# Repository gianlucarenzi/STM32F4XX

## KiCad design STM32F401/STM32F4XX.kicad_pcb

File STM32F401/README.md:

# STM32F401 Generic Module

A generic development board for the STM32F401 microcontroller.

## Overview

This project provides a development board for the STM32F401RCT6 microcontroller in a LQFP-64 package. The board is designed to be a standard platform for developing and prototyping applications with this MCU. It includes basic components and connectors to get started quickly.

## Features

*   STM32F401RCT6 microcontroller
*   USB-C connector for power and data
*   SWD connector for programming and debugging
*   Reset button
*   JP1 jumper (for DFU mode)
*   User LED
*   Power LED
*   Expansion headers for all MCU pins

## Images

**Board Top**

**Board Bottom**

**Board Schematics**

## Hardware

The hardware design is done in KiCad. You can find the project files in this repository.

*   **Schematic:** [STM32F4XX.sch](STM32F4XX.sch)
*   **PCB Layout:** [STM32F4XX.kicad_pcb](STM32F4XX.kicad_pcb)
*   **KiCad Project:** [STM32F4XX.pro](STM32F4XX.pro)
*   **Schematics PDF (Autogenerated):** [STM32F4XX.pdf](STM32F4XX.pdf)

### Manufacturing Files

Gerber and production files for JLCPCB are available in the `production` directory and in the following archives:

*   **Gerbers:** [STM32F401-gerbers.zip](STM32F401-gerbers.zip)
*   **BOM for JLCPCB:** [STM32F4XX-v2.0-JLCPCB-BOM.csv](STM32F4XX-v2.0-JLCPCB-BOM.csv)
*   **CPL for JLCPCB:** [STM32F4XX-v2.0-JLCPCB-CPL.csv](STM32F4XX-v2.0-JLCPCB-CPL.csv)

## Firmware

The firmware for the HID bootloader is located in the `STM32_HID_Bootloader` directory. It is based on the STM32 HAL library.

*   **Bootloader Source Code:** [STM32_HID_Bootloader/](STM32_HID_Bootloader/)

## Getting Started

To get started with this project, you will need:

1.  A text editor or IDE for firmware development (e.g., VSCode with PlatformIO, STM32CubeIDE).
2.  An ST-Link v2 programmer/debugger.
3.  A USB-C cable.

### Building and Flashing

1.  Clone this repository.
2.  Open the `STM32_HID_Bootloader` directory in your IDE.
3.  Build the project.
4.  Connect the ST-Link to the SWD connector on the board.
5.  Flash the firmware to the MCU.

## Contributing

Contributions are welcome! Please feel free to submit a pull request or open an issue if you find any problems or have suggestions for improvements.

## License

This project is licensed under the MIT License. See the [LICENSE](LICENSE) file for details.

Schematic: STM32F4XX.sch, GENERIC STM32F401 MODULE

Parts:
C1, C2, C3, C4, C5, C7, C11, C12, C13: 100nF; C_0603_1608Metric_Pad1.08x0.95mm_HandSolder; LCSC C524962
C6, C14: 10uF; CP_EIA-3528-12_Kemet-T_Pad1.50x2.35mm_HandSolder; LCSC C8017
C8: 4.7uF; C_0805_2012Metric_Pad1.18x1.45mm_HandSolder; LCSC C7393930
C9, C10: 22pF; C_0603_1608Metric_Pad1.08x0.95mm_HandSolder; LCSC C105620
H1, H2, H3, H4: MountingHole_Pad; MountingHole_3.2mm_M3_DIN965_Pad
J1: DEBUG UART; PinHeader_1x03_P2.54mm_Vertical
J2, J4: CONN_02x16_PIN_SMD_Odd_Even_2.54mm; PinHeader_2x16_P2.54mm_Vertical_SMD; LCSC C6332241
J3: DX07S016JA1R1500; JAE_DX07S016JA1R1500; PARTREV 1; LCSC C3197885
J5: CONN_SMD_HEADER_BOX_02x05_Odd_Even_2.54mm; IDC-Header_2x05_P2.54mm_Vertical_SMD; LCSC C492446
JP1: ~BOOTLOADER; PinHeader_1x02_P2.54mm_Vertical
L1: 90R@100MHZ; L_0805_2012Metric_Pad1.15x1.40mm_HandSolder; LCSC C50325938
LD1: RED; LED_1206_3216Metric_Pad1.42x1.75mm_HandSolder; LCSC C965822
LD2: GREEN; LED_0805_2012Metric_Pad1.15x1.40mm_HandSolder; LCSC C84260
LOGO1: OSH; OSHW-Logo_11.4x12mm_SilkScreen
LOGO2: designed with KiCAD; KiCad-Logo2_6mm_SilkScreen
R1: 10K; R_0603_1608Metric_Pad0.98x0.95mm_HandSolder; LCSC C25804
R2, R9: 0R; R_0603_1608Metric_Pad0.98x0.95mm_HandSolder; LCSC C2906974
R3, R6: 5K1; R_0603_1608Metric_Pad0.98x0.95mm_HandSolder; LCSC C23186
R4, R5: 22R; R_0603_1608Metric_Pad0.98x0.95mm_HandSolder; LCSC C23345
R7: 330R; R_0603_1608Metric_Pad0.98x0.95mm_HandSolder; LCSC C105881
R8: 470R; R_0603_1608Metric_Pad0.98x0.95mm_HandSolder; LCSC C114669
SW1: ~RESET; SPST-7.3x3.9x2.5-WUERTH-434121025816; LCSC C318911
U1: STM32F401RCT6; LQFP-64_10x10mm_P0.5mm; LCSC C74524
U2: AMS1117-3.3; SOT-223-3_TabPin2; LCSC C6186
Y1: 8MHzC; Crystal_SMD_HC49-SD; LCSC C12674

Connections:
+3V3: C1.1, C2.1, C3.1, C4.1, C13.1, C14.1, J2.5, J2.7, J4.26, J4.28, J5.8, L1.1, LD1.2, R1.1, U1.19 (VDD), U1.32 (VDD), U1.48 (VDD), U1.64 (VDD), U2.2
/ANALOG_VDD: C5.1, C6.1, L1.2, U1.13 (VREF+)
/DM: J3.5, J3.8, R5.2
/DP: J3.6, J3.7, R4.2
/VSSA: C5.2, C6.2, R2.2, U1.12 (VSSA)
A0: J2.29, R9.1, U1.14 (PA0)
A1: J2.32, U1.15 (PA1)
A2: J1.3, J2.31, U1.16 (PA2)
A3: J1.2, J4.25, U1.17 (PA3)
A4: J4.24, U1.20 (PA4)
A5: J4.23, U1.21 (PA5)
A6: J4.22, U1.22 (PA6)
A7: J4.21, U1.23 (PA7)
A8: J4.6, U1.41 (PA8)
A9: J4.5, U1.42 (PA9)
A10: J4.4, U1.43 (PA10)
A11: J4.3, R5.1, U1.44 (PA11)
A12: J4.2, R4.1, U1.45 (PA12)
A13: J4.1, J5.4, U1.46 (PA13)
A14: J2.9, J5.2, U1.49 (PA14)
A15: J2.12, U1.50 (PA15)
B0: J4.18, U1.26 (PB0)
B1: J4.17, U1.27 (PB1)
B2: J4.16, U1.28 (PB2)
B3: J2.15, U1.55 (PB3)
B4: J2.18, U1.56 (PB4)
B5: J2.17, U1.57 (PB5)
B6: J2.20, U1.58 (PB6)
B7: J2.19, U1.59 (PB7)
B8: J2.22, U1.61 (PB8)
B9: J2.21, U1.62 (PB9)
B10: J4.15, U1.29 (PB10)
B12: J4.14, U1.33 (PB12)
B13: J4.13, U1.34 (PB13)
B14: J4.12, U1.35 (PB14)
B15: J4.11, U1.36 (PB15)
C0: J2.25, U1.8 (PC0)
C1: J2.28, JP1.2, U1.9 (PC1)
C2: J2.27, U1.10 (PC2)
C3: J2.30, U1.11 (PC3)
C4: J4.20, U1.24 (PC4)
C5: J4.19, U1.25 (PC5)
C6: J4.10, U1.37 (PC6)
C7: J4.9, U1.38 (PC7)
C8: J4.8, U1.39 (PC8)
C9: J4.7, U1.40 (PC9)
C10: J2.11, U1.51 (PC10)
C11: J2.14, U1.52 (PC11)
C12: J2.13, U1.53 (PC12)
C13: J2.24, U1.2 (PC13)
C14: J2.23, U1.3 (PC14)
C15: J2.26, U1.4 (PC15)
D2: J2.16, U1.54 (PD2)
GND: C1.2, C2.2, C3.2, C4.2, C7.2, C8.2, C9.2, C10.2, C11.1, C12.2, C13.2, C14.2, H1.1, H2.1, H3.1, H4.1, J1.1, J2.1, J2.2, J2.3, J2.4, J3.1, J3.12, J4.29, J4.30, J4.31, J4.32, J5.5, J5.6, JP1.1, R2.1, R3.1, R6.2, R7.2, R8.2, SW1.1, U1.1 (VBAT), U1.18 (VSS), U1.31 (VSS), U1.47 (VSS), U1.60 (BOOT0), U1.63 (VSS), U2.1
unnamed: C7.1, R1.2, SW1.2, U1.7 (NRST)
unnamed: C8.1, U1.30 (VCAP1)
unnamed: C9.1, U1.5 (PH0), Y1.1
unnamed: C10.1, U1.6 (PH1), Y1.2
unnamed: C11.2, J3.S1, J3.S2, J3.S3, J3.S4, J3.S5, J3.S6
unnamed: J3.3, R3.2
unnamed: J3.9, R6.1
unnamed: LD1.1, R7.1
unnamed: LD2.1, R8.1
unnamed: LD2.2, R9.2
VCC: C12.1, J2.6, J2.8, J3.2, J3.11, J4.27, U2.3

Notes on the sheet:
POWER INPUT IS 5VDC
BOOT0 Boot from internal FLASH
ANALOG VOLTAGE FILTER
POWER SECTION 5V INPUT 3.3V OUTPUT 800mA
BYPASS FILTER CAPACITORS
DEBUG UART TTL RS232 115200 8N1
USB C / USB DEVICE
ST-LINK v2 PROGRAMMING SWDIO SWCLK
CLOSE TO FORCE BOOTLOADER MODE
ACTIVITY LED Can be disabled

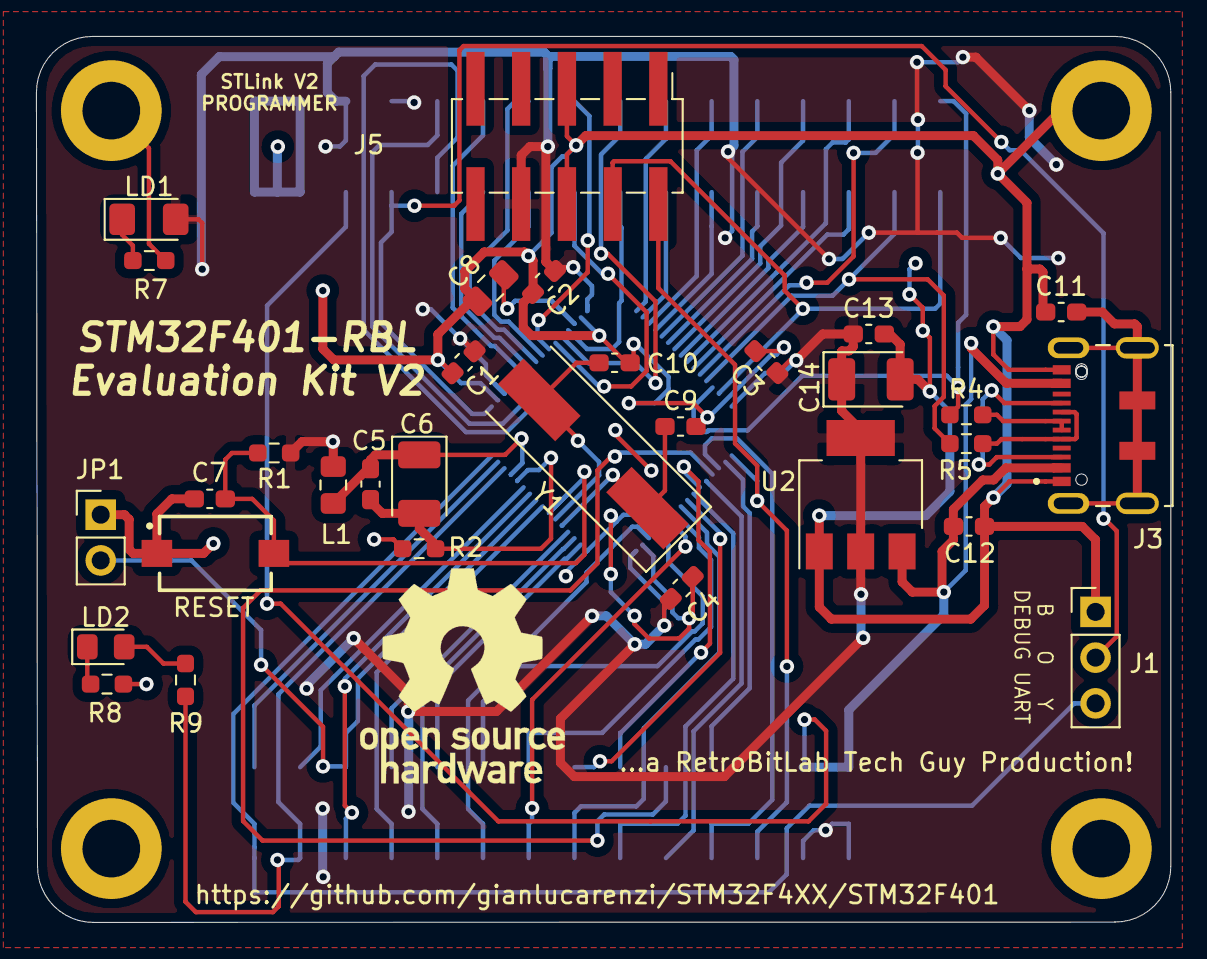
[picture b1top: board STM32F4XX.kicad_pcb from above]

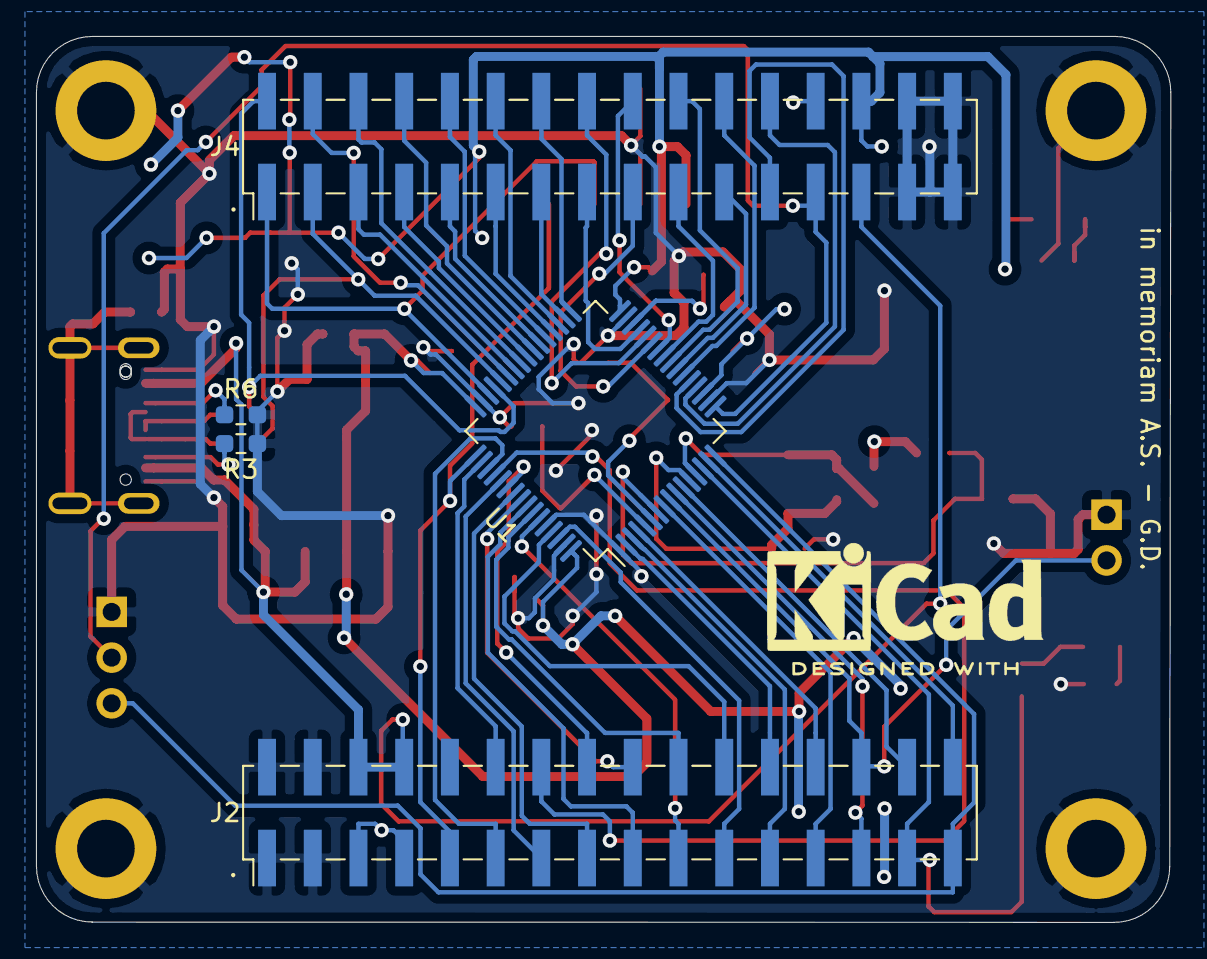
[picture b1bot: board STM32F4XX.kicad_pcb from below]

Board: 2 copper layers, 63.0 x 49.2 mm, 42 parts (6 on the bottom side), 65 nets.

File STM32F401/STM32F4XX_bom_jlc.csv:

"Comment","Designator","Footprint","LCSC Part #"
"LM1117-3.3","U2","","C126027 "
"4.7uF","C8","","C7237 "
"~RESET","SW1","","C318911"
"10K","R1","","C17902"
"10uF","C6 C13","","C108529 "
"100uH","FB1","","C128802"
"0R","R2","","C17888"
"100nF","C1 C2 C3 C4 C7 C5 C12 C11","","C24497"
"22pF","C9 C10",""," C1896 "
"DEBUG UART","J1","",""
"8MHz","Y1","","C107426"
"USB_B_Mini","J3","","C69074"
"22R","R4 R3","","C114943"
"JTAG SWDIO SWCLK","J5","",""
"STM32F401RCT6","U1","","C74524"
"RED","D1","","C93133"
"330R","R5","","C245520 "
"Conn_02x16_Counter_Clockwise","J4 J2","",""

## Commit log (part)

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2022-01-11 Sent to JLCPCB for production (missing some silkscreen information)
2022-01-11 Schematic added
2022-01-11 Removed unused backup Added Schematics
2022-01-11 Created from JLCPCB tools installed (pip)
2022-01-11 Removed
2022-01-11 Added
2022-01-11 Modified for JLCPCB production and added some silkscreens
2022-01-11 Production files sent to JLCPCB for SMT assembly and PCB manufacturing (missing some silkscreen information)
2022-01-11 Mechanical Drawings stuff
2022-01-11 Added some comments
2022-01-11 Updated with the new slikscreens
2022-01-11 Updated with the new slikscreens & comments
2022-02-04 Updated fp info cache with STM32F401-DK
2022-02-05 Interactive BOM for manual soldering
2022-02-05 3D objects (mechanical and infos)
2022-02-05 Added KiCAD logo on back silkscreen
2022-02-05 Added KiCAD loAdded KiCAD logo on back silkscreen
2022-02-05 Updated without silkscreen data on back. Only strings
2022-02-05 Autogenerated.
2022-02-05 Ultra simple JLCPCB LCSC Part selection.
2022-02-05 Script to create JLCPCB as the export tool in schematics.
2022-02-05 Autogenerated
2022-02-05 Ignored the csv autogenerated. They are separate as top and bottom
2022-02-05 Sent to JLCPCB
2022-02-05 Added RESET switch
2022-02-07 Updated footprint for RESET switch. It will a 7.3x3.9x2.5 mm like a Wuerth 434121025816
2022-02-07 Generated
2022-02-08 Updated for new RESET switch as per JLCPCB request. E-mail beginning of Feb.2022
2022-02-08 Rotated. Strangely JLCPCB gives me the wrong orientation for this...
2022-02-08 Ignore bak files
2022-02-08 New revision 0.3
2022-11-05 Imported from Serasidis/STM32_HID_Bootloader
2022-11-05 Bootloader mode: powerup with ESC + LCTRL + SPACEBAR PRESSED within 2 seconds
2023-02-15 Modified the USB+ and USB- pins. BOY UART
2023-02-15 V0.4 USB+ and USB- bug, BOY UART
2023-02-16 Bootloader for DFU
2023-02-16 Mandatory PINS: GPIOA0 for LED (ground means ON) GPIOC1 for BOOT MODE (ground for 1 second at startup means DFU MODE)
2023-02-16 Cleanup
2023-02-18 Usage of GNU linker script symbols
2023-02-18 FWVER: v0.3 BUILD: 15:22:54-Feb 18 2023
2023-02-18 Update README.md
    Added some markup for code
2023-02-18 Ignore the TOO BIG Files STM32Cube-Programmer for various Operating Systems
2023-02-18 All symbols
2023-02-18 PULL UP on USB_DP
2023-02-18 Clean up
2023-02-18 Ignore build directory
2023-05-10 Committed. If it is wrong I will change it again later.
2025-10-12 For OpenOCD setup
2025-10-30 Start transition to a smaller board. Using smallest components footprint
2025-11-01 RetroBitLab library instead of AmigaComponents
2025-11-03 Added .gitignore
2025-11-03 Like in stalker
2025-11-03 Added for clearity
2025-11-03 New board. Smaller
2025-11-03 Ignored the compiled tools
2025-11-03 Added for autogeneration
2025-11-03 First try with an autorouter. Completed by hand
2025-11-03 Autogeneration
2025-11-03 Not needed
2025-11-03 Used for creating footprint of STM32F4XX_BOARD
2025-11-03 V2.0 Smaller
2025-11-03 Ignored for autogeration
2025-11-03 Removed. Not needed for autogeneration
2025-11-03 BOOT0 was wrong
2025-11-03 Update the firmware folder too
2025-11-03 Added openocd script for flashing with STLink V2
2025-11-03 Added VSCode configuration files for STM32 HID Bootloader project
2025-11-03 fp-info-cache ignored
2025-11-12 From other projects
2025-11-12 Jump with interrupts disabled
2025-11-17 unused
2025-11-17 Added and adapted from STALKER BOOTLOADER
2025-11-17 Renamed Added panic()
2025-11-17 Updated to latest running version
